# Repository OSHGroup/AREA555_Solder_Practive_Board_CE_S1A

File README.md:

Area-555-Solder-Board
=====================

Area 555's practice soldering board repo.

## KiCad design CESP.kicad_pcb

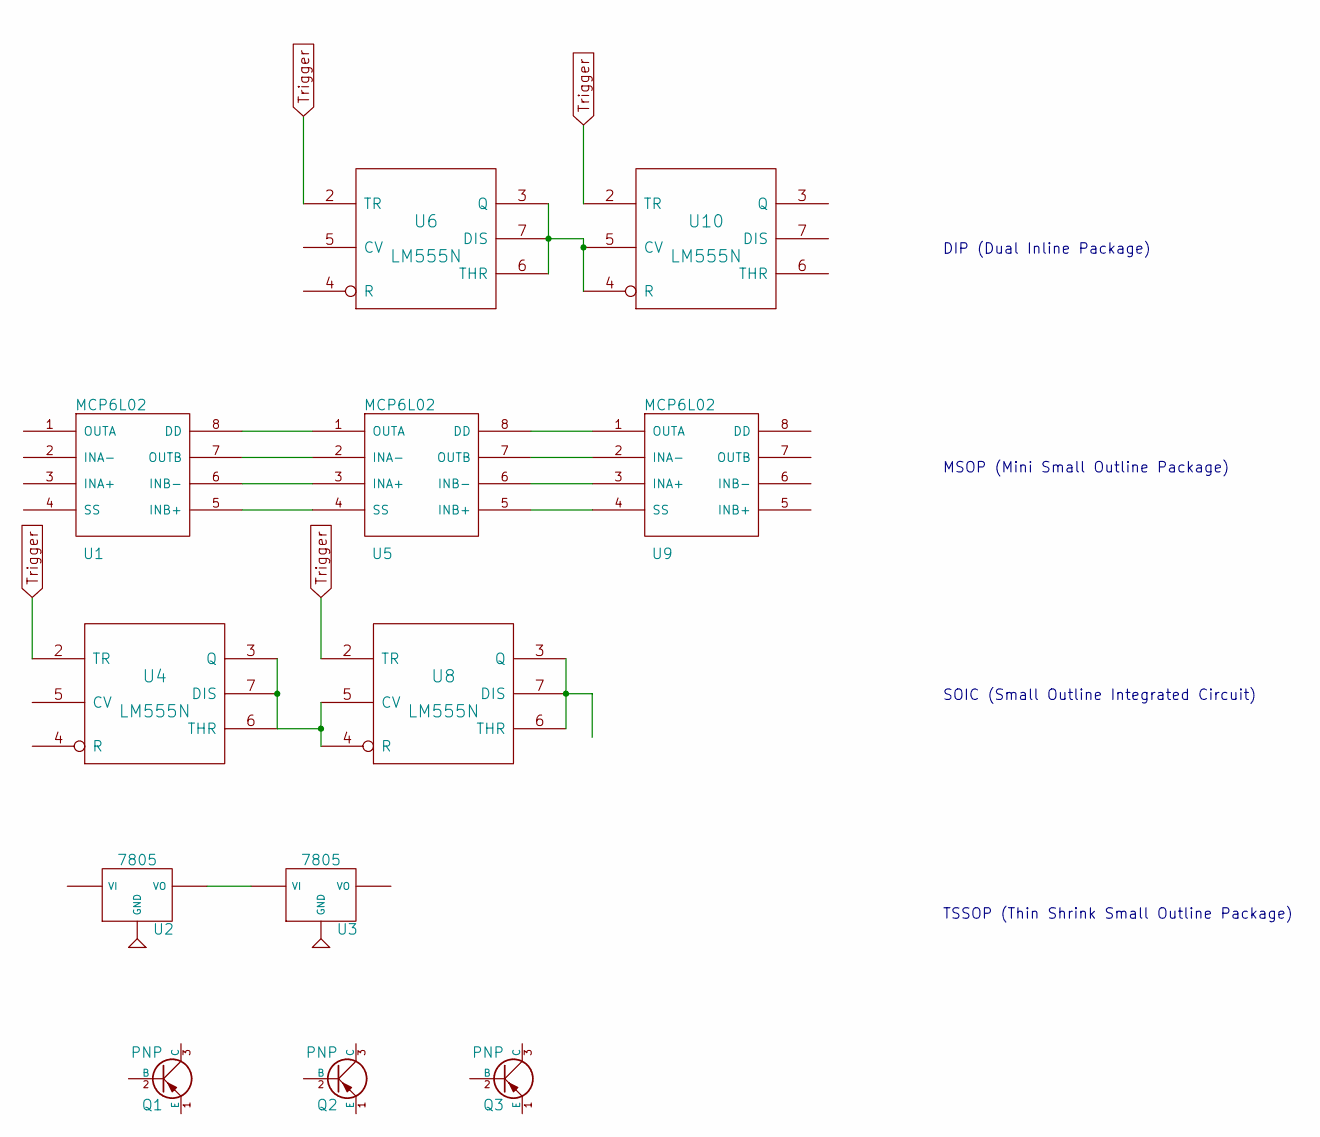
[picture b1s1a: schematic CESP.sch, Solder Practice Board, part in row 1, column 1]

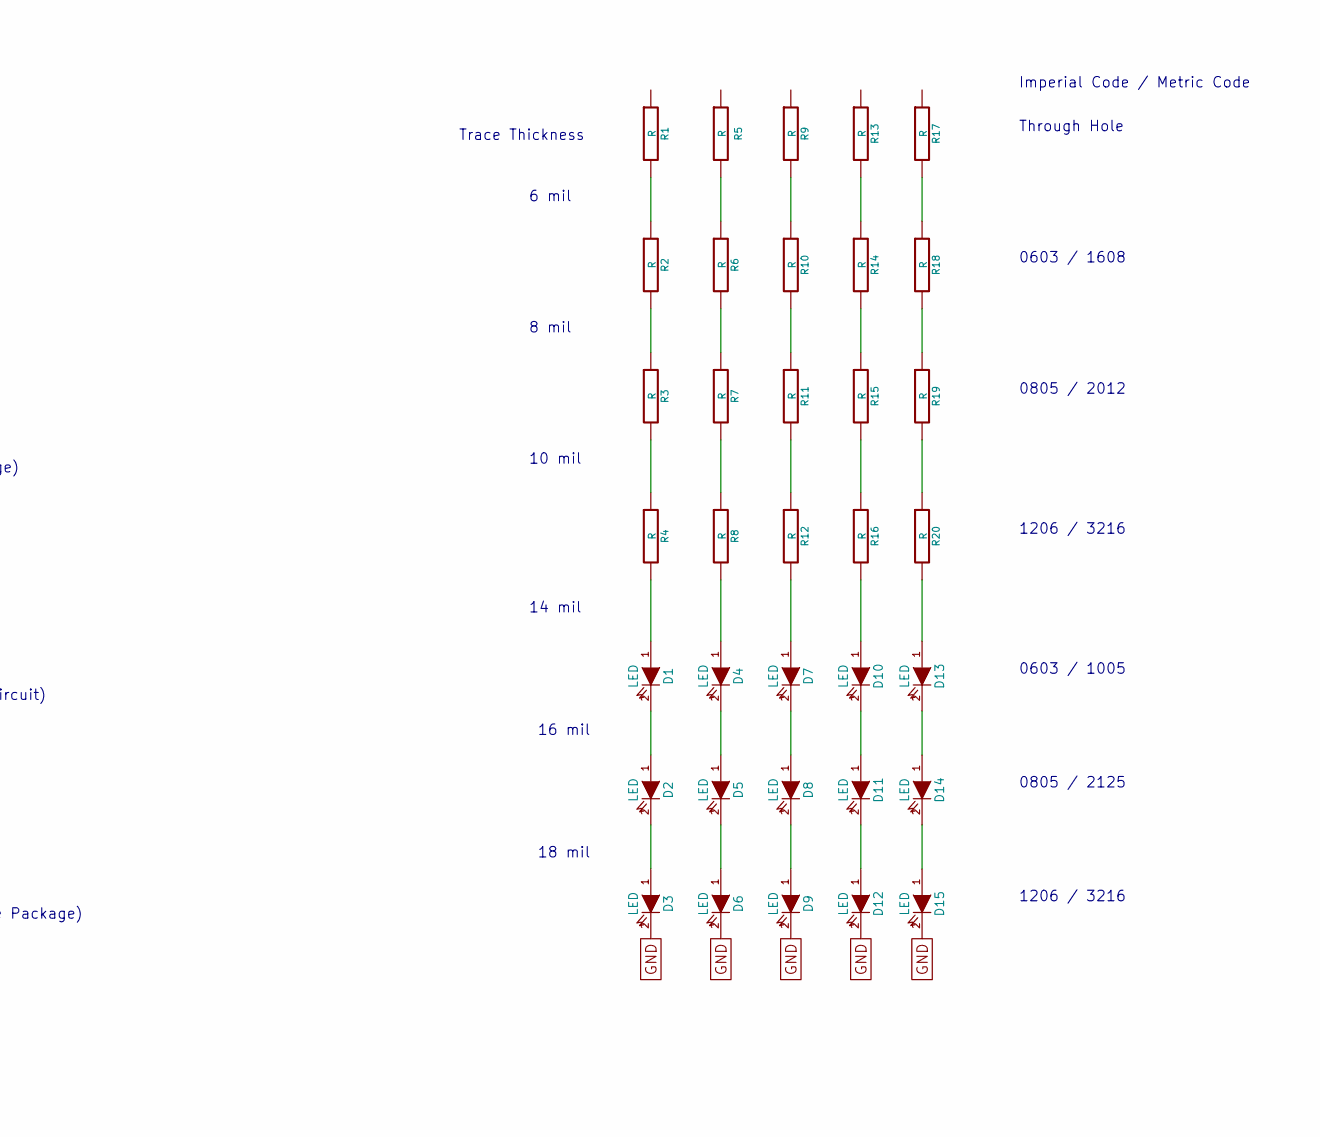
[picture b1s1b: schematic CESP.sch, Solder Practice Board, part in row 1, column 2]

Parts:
D1, D2, D3, D4, D5, D6, D7, D8, D9, D10, D11, D12, D13, D14, D15: LED
Q1, Q2, Q3: PNP
R1, R2, R3, R4, R5, R6, R7, R8, R9, R10, R11, R12, R13, R14, R15, R16, R17, R18, R19, R20: R
U1, U5, U9: MCP6L02
U2, U3: 7805
U4, U6, U8, U10: LM555N

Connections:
GND: D3.2 (K), D6.2 (K), D9.2 (K), D12.2 (K), D15.2 (K), U4.1 (GND), U6.1 (GND), U8.1 (GND), U10.1 (GND)
unnamed: U4.3 (Q), U4.6 (THR), U4.7 (DIS), U8.4 (R), U8.5 (CV)
unnamed: U8.3 (Q), U8.6 (THR), U8.7 (DIS)
unnamed: D1.1 (A), R4.2
unnamed: D4.1 (A), R8.2
unnamed: D7.1 (A), R12.2
unnamed: D10.1 (A), R16.2
unnamed: D13.1 (A), R20.2
unnamed: D13.2 (K), D14.1 (A)
unnamed: D10.2 (K), D11.1 (A)
unnamed: D7.2 (K), D8.1 (A)
unnamed: D4.2 (K), D5.1 (A)
unnamed: D1.2 (K), D2.1 (A)
unnamed: U5.8 (DD), U9.1 (OUTA)
unnamed: U6.3 (Q), U6.6 (THR), U6.7 (DIS), U10.4 (R), U10.5 (CV)
unnamed: U1.6 (INB-), U5.3 (INA+)
unnamed: U1.7 (OUTB), U5.2 (INA-)
unnamed: U1.8 (DD), U5.1 (OUTA)
unnamed: U1.5 (INB+), U5.4 (SS)
unnamed: U5.7 (OUTB), U9.2 (INA-)
unnamed: U5.6 (INB-), U9.3 (INA+)
unnamed: U5.5 (INB+), U9.4 (SS)
unnamed: D14.2 (K), D15.1 (A)
unnamed: R13.2, R14.1
unnamed: R17.2, R18.1
unnamed: R5.2, R6.1
unnamed: R1.2, R2.1
unnamed: R9.2, R10.1
unnamed: R3.2, R4.1
unnamed: R18.2, R19.1
unnamed: R19.2, R20.1
unnamed: R14.2, R15.1
unnamed: R15.2, R16.1
unnamed: R10.2, R11.1
unnamed: R11.2, R12.1
unnamed: R6.2, R7.1
unnamed: R7.2, R8.1
unnamed: R2.2, R3.1
unnamed: D11.2 (K), D12.1 (A)
unnamed: D2.2 (K), D3.1 (A)
unnamed: D5.2 (K), D6.1 (A)
unnamed: D8.2 (K), D9.1 (A)
Trigger: U4.2 (TR), U6.2 (TR), U8.2 (TR), U10.2 (TR)
VCC: U4.8 (VCC), U6.8 (VCC), U8.8 (VCC), U10.8 (VCC)

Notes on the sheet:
MSOP (Mini Small Outline Package)
TSSOP (Thin Shrink Small Outline Package)
SOIC (Small Outline Integrated Circuit)
DIP (Dual Inline Package)
Imperial Code / Metric Code
Through Hole
0603 / 1608
0805 / 2012
0603 / 1005
0805 / 2125
1206 / 3216
6 mil
8 mil
10 mil
14 mil
Trace Thickness
16 mil
18 mil

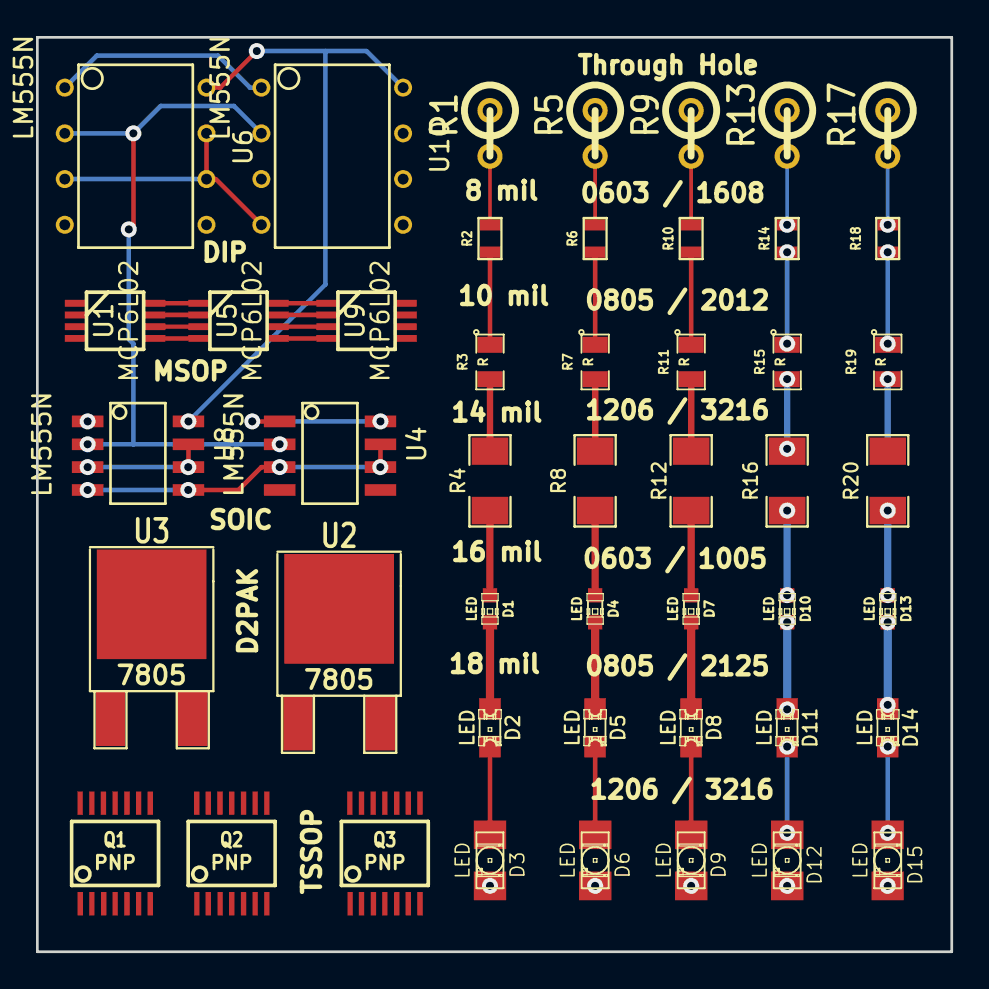
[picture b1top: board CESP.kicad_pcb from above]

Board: 2 copper layers, 50.8 x 50.8 mm, 47 parts (0 on the bottom side), 44 nets.

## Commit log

2014-01-31 First Go
    Blindly trying..why the heck not!
2014-01-31 Revert "First Go"
    This reverts commit 86b047847ba1f24d5d382c057e9c9dbe8023fbc6.
2014-01-31 Second Go
    All the files should be here now...I Hope
